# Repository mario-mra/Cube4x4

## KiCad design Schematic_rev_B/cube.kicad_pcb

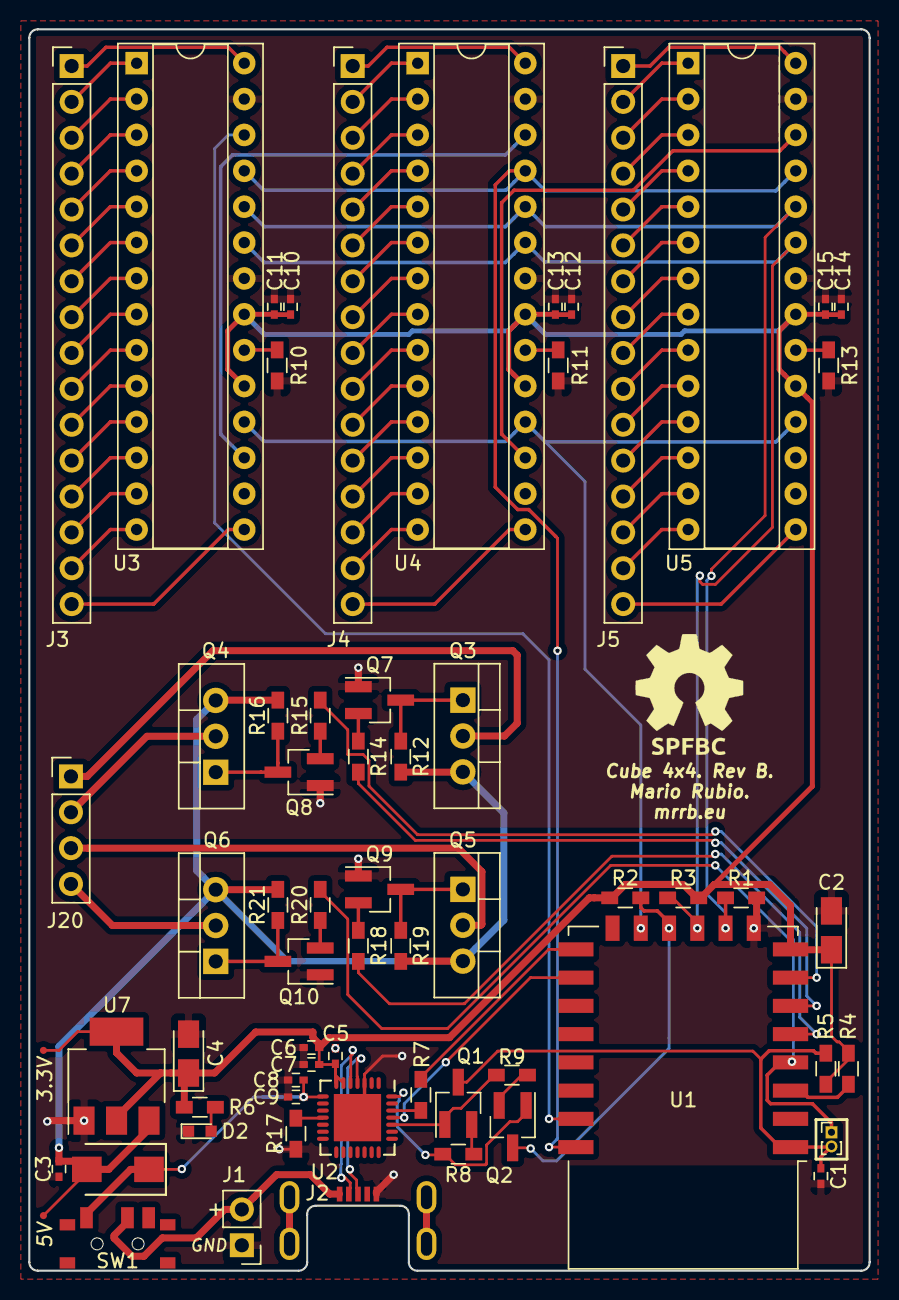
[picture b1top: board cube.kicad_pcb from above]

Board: 2 copper layers, 59.5 x 87.9 mm, 64 parts (0 on the bottom side), 93 nets.

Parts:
C1, C6, C9, C11, C13, C15: 100nF; C_0402
C2, C4: 22uF; CP_Tantalum_Case-A_EIA-3216-18_Reflow
C3, C7, C10, C12, C14: 4.7uF; C_0402
C5, C8: 4.7Uf; C_0402
D1: 1N5819-SS14; DO-214AC
D2: Power_LED; LED_0603
J1: Conn_01x02; Pin_Header_Straight_1x02_Pitch2.54mm
J2: USB_B; Micro_USB_Female_Ali
J3: RED_conn; Pin_Header_Straight_1x16_Pitch2.54mm
J4: GREEN_conn; Pin_Header_Straight_1x16_Pitch2.54mm
J5: BLUE_conn; Pin_Header_Straight_1x16_Pitch2.54mm
J7: TP_V5; Measurement_Point_Round-SMD-Pad_Small
J8: TP_V3.3; Measurement_Point_Round-SMD-Pad_Small
J20: ANODE_conn; Pin_Header_Straight_1x04_Pitch2.54mm
JP1: Jumper; Pin_Header_Straight_1x02_Pitch1.00mm
Q1, Q2, Q7, Q8, Q9, Q10: S8050; SOT-23_Handsoldering
Q3, Q4, Q5, Q6: IRF9540N; TO-220-3_Vertical
R1, R2, R3, R4, R5, R8, R9: 12k; R_0603_HandSoldering
R6: 200; R_0603_HandSoldering
R7: 470; R_0603_HandSoldering
R10, R11, R13: 2K; R_0603_HandSoldering
R12, R16, R19, R21: 1K; R_0603_HandSoldering
R14, R15, R17, R18, R20: 12K; R_0603_HandSoldering
SW1: SW_SPDT; Switch_1P2T_SPDT_Ali
U1: ESP-12E
U2: CP2102; QFN-28-1EP_5x5mm_Pitch0.5mm
U3, U4, U5: TLC5940NT; DIP-28_W7.62mm_Socket
U7: LM1117-3.3; SOT-223-3_TabPin2

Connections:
/A0: J20.1, Q3.2
/A1: J20.2, Q4.2
/A2: J20.3, Q5.2
/A3: J20.4, Q6.2
/B0: J5.1, U5.28
/B1: J5.2, U5.1
/B2: J5.3, U5.2
/B3: J5.4, U5.3
/B4: J5.5, U5.4
/B5: J5.6, U5.5
/B6: J5.7, U5.6
/B7: J5.8, U5.7
/B8: J5.9, U5.8
/B9: J5.10, U5.9
/B10: J5.11, U5.10
/B11: J5.12, U5.11
/B12: J5.13, U5.12
/B13: J5.14, U5.13
/B14: J5.15, U5.14
/B15: J5.16, U5.15
/G0: J4.1, U4.28
/G1: J4.2, U4.1
/G2: J4.3, U4.2
/G3: J4.4, U4.3
/G4: J4.5, U4.4
/G5: J4.6, U4.5
/G6: J4.7, U4.6
/G7: J4.8, U4.7
/G8: J4.9, U4.8
/G9: J4.10, U4.9
/G10: J4.11, U4.10
/G11: J4.12, U4.11
/G12: J4.13, U4.12
/G13: J4.14, U4.13
/G14: J4.15, U4.14
/G15: J4.16, U4.15
/R0: J3.1, U3.28
/R1: J3.2, U3.1
/R2: J3.3, U3.2
/R3: J3.4, U3.3
/R4: J3.5, U3.4
/R5: J3.6, U3.5
/R6: J3.7, U3.6
/R7: J3.8, U3.7
/R8: J3.9, U3.8
/R9: J3.10, U3.9
/R10: J3.11, U3.10
/R11: J3.12, U3.11
/R12: J3.13, U3.12
/R13: J3.14, U3.13
/R14: J3.15, U3.14
/R15: J3.16, U3.15
/USB_UART/D+: J2.3, U2.4
/USB_UART/D-: J2.2, U2.5
BLANK: R3.1, U1.11, U3.23, U4.23, U5.23
CH_PD: R4.1, U1.3
DTR: Q2.1, R8.2, U2.28
GND: C1.1, C2.2, C3.2, C4.2, C5.2, C6.2, C7.1, C8.1, C9.1, C10.1, C11.1, C12.1, C13.1, C14.1, C15.1, D2.1, J1.1, J2.4, Q7.1, Q8.1, Q9.1, Q10.1, R1.2, R10.2, R11.2, R13.2, R17.2, U1.9, U2.3, U2.29, U3.22, U3.27, U4.22, U4.27, U5.22, U5.27, U7.1
GPIO0: Q2.3, R2.1, U1.12
GPIO4: U1.13, U3.18, U4.18, U5.18
GPIO12: R14.2, U1.6
GPIO13: R15.2, U1.7
GPIO14: R18.2, U1.5
GPIO15: R1.1, U1.10, U3.24, U4.24, U5.24
GPIO16: JP1.1, R20.2, U1.4
MOSI: U1.21, U3.26
unnamed: D2.2, R6.2
unnamed: J1.2, J2.1, SW1.2
unnamed: Q1.2, R8.1
unnamed: Q2.2, R9.1
unnamed: Q3.1, Q7.3, R12.1
unnamed: Q4.1, Q8.3, R16.1
unnamed: Q5.1, Q9.3, R19.1
unnamed: Q7.2, R14.1
unnamed: Q8.2, R15.1
unnamed: Q9.2, R18.1
unnamed: Q10.2, R20.1
unnamed: Q6.1, Q10.3, R21.1
unnamed: R7.1, U2.26
unnamed: R10.1, U3.20
unnamed: R11.1, U4.20
unnamed: R13.1, U5.20
unnamed: R17.1, U2.11
REST: C1.2, JP1.2, Q1.3, R5.1, U1.1
RTS: Q1.1, R9.2, U2.24
RXD: U1.16, U2.25
SCLK: U1.22, U3.25, U4.25, U5.25
TLC_S2: U3.17, U4.26
TLC_S3: U4.17, U5.26
TXD: R7.2, U1.15
V3.3: C2.1, C4.1, C5.1, C6.1, C7.2, C10.2, C11.2, C12.2, C13.2, C14.2, C15.2, J8.1, R2.2, R3.2, R4.2, R5.2, R6.1, U1.8, U2.6, U2.7, U3.19, U3.21, U4.19, U4.21, U5.19, U5.21, U7.2
V5: C3.1, D1.1, J7.1, Q3.3, Q4.3, Q5.3, Q6.3, R12.2, R16.2, R19.2, R21.2, U7.3
Vin: C8.2, C9.2, D1.2, SW1.3, U2.8

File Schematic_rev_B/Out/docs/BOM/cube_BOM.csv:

"Id";"Designator";"Package";"Quantity";"Designation";"Supplier and ref";
1;"J2";"Micro_USB_Female_Ali";1;"USB_B";;;
2;"D1";"DO-214AC";1;"1N5819-SS14";;;
3;"SW1";"Switch_1P2T_SPDT_Ali";1;"SW_SPDT";;;
4;"R1,R2,R5,R4,R3,R8,R9";"R_0603_HandSoldering";7;"12k";;;
5;"C10,C12,C3,C7,C14";"C_0402";5;"4.7uF";;;
6;"R11,R10,R13";"R_0603_HandSoldering";3;"2K";;;
7;"C15,C1,C6,C9,C11,C13";"C_0402";6;"100nF";;;
8;"C2,C4";"CP_Tantalum_Case-A_EIA-3216-18_Reflow";2;"22uF";;;
9;"C5,C8";"C_0402";2;"4.7Uf";;;
10;"D2";"LED_0603";1;"Power_LED";;;
11;"J1";"Pin_Header_Straight_1x02_Pitch2.54mm";1;"Conn_01x02";;;
12;"J3";"Pin_Header_Straight_1x16_Pitch2.54mm";1;"RED_conn";;;
13;"J4";"Pin_Header_Straight_1x16_Pitch2.54mm";1;"GREEN_conn";;;
14;"J5";"Pin_Header_Straight_1x16_Pitch2.54mm";1;"BLUE_conn";;;
15;"J20";"Pin_Header_Straight_1x04_Pitch2.54mm";1;"ANODE_conn";;;
16;"Q1,Q2,Q7,Q8,Q9,Q10";"SOT-23_Handsoldering";6;"S8050";;;
17;"Q3,Q4,Q5,Q6";"TO-220-3_Vertical";4;"IRF9540N";;;
18;"R6";"R_0603_HandSoldering";1;"200";;;
19;"R7";"R_0603_HandSoldering";1;"470";;;
20;"R12,R16,R19,R21";"R_0603_HandSoldering";4;"1K";;;
21;"R14,R15,R17,R18,R20";"R_0603_HandSoldering";5;"12K";;;
22;"U1";"ESP-12E";1;"ESP-12E";;;
23;"U2";"QFN-28-1EP_5x5mm_Pitch0.5mm";1;"CP2102";;;
24;"U3,U4,U5";"DIP-28_W7.62mm_Socket";3;"TLC5940NT";;;
25;"U7";"SOT-223-3_TabPin2";1;"LM1117-3.3";;;
26;"JP1";"Pin_Header_Straight_1x02_Pitch1.00mm";1;"Jumper";;;
27;"J7";"Measurement_Point_Round-SMD-Pad_Small";1;"TP_V5";;;
28;"J8";"Measurement_Point_Round-SMD-Pad_Small";1;"TP_V3.3";;;

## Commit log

2018-09-06 Added Schematic REV_B
